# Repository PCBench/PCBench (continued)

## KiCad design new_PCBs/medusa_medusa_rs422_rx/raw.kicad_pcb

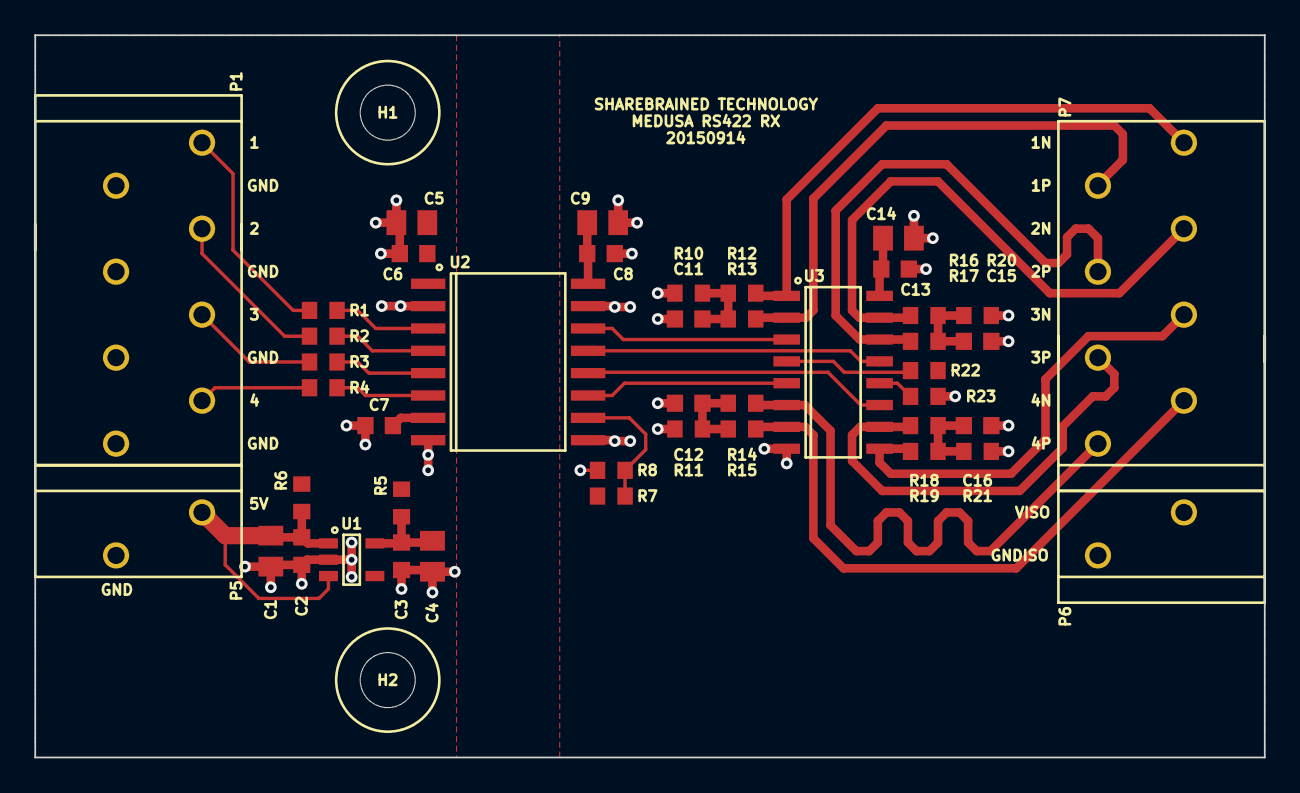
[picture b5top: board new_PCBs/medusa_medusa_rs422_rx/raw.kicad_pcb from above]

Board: 2 copper layers, 71.5 x 42.0 mm, 46 parts (0 on the bottom side), 33 nets.

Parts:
C1, C4: DNI; IPC_CAPC2012X140N
C2, C3: DNI; IPC_CAPC1608X95N
C5, C9, C14: 10U; IPC_CAPC2012X140N
C6, C7, C8, C13: 100N; IPC_CAPC1608X95N
C11, C12, C15, C16: 10N; IPC_CAPC1608X95N
H1, H2: HOLE; HOLE_3P2MM
P1, P7: TERM8; 1990067
P5, P6: TERM2; 1990009
R1, R2, R3, R4: 22R; IPC_RESC1608X55N
R5, R7, R10, R11, R20, R21: DNI; IPC_RESC1608X55N
R6, R8, R22, R23: 0R; IPC_RESC1608X55N
R12, R13, R14, R15, R16, R17, R18, R19: 50R; IPC_RESC1608X55N
U1: DNI; IPC_SOT95P280X110-5N
U2: ADuM6404; IPC_SOIC127P1030X265-16N
U3: AM26LV32E; IPC_SOIC127P600X175-16N

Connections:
+3.3V: C3.1, C4.1, R5.2, U1.5
+5V: C1.1, C2.1, P5.2, R6.2, U1.1, U1.3
/GNDISO: C8.2, C9.2, C11.1, C12.1, C13.2, C14.2, C15.2, C16.2, P6.2, R8.2, R10.1, R11.1, R20.2, R21.2, R23.2, U2.9, U2.15, U3.8
/RX1: R1.1, U2.3
/RX1ISO: U2.14, U3.3
/RX1N: P7.1, R12.2, U3.1
/RX1P: P7.2, R13.2, U3.2
/RX1R: P1.8, R1.2
/RX2: R2.1, U2.4
/RX2ISO: U2.13, U3.13
/RX2N: P7.3, R16.1, U3.15
/RX2P: P7.4, R17.1, U3.14
/RX2R: P1.6, R2.2
/RX3: R3.1, U2.5
/RX3ISO: U2.12, U3.11
/RX3N: P7.5, R19.1, U3.9
/RX3P: P7.6, R18.1, U3.10
/RX3R: P1.4, R3.2
/RX4: R4.1, U2.6
/RX4ISO: U2.11, U3.5
/RX4N: P7.7, R15.2, U3.7
/RX4P: P7.8, R14.2, U3.6
/RX4R: P1.2, R4.2
/RXG: R22.2, U3.4
/RXG#: R23.1, U3.12
/VDD1: C5.1, C6.1, C7.1, R5.1, R6.1, U2.1, U2.7
/VISO: C8.1, C9.1, C13.1, C14.1, P6.1, R7.2, R22.1, U2.16, U3.16
/VSEL: R7.1, R8.1, U2.10
GND: C1.2, C2.2, C3.2, C4.2, C5.2, C6.2, C7.2, P1.1, P1.3, P1.5, P1.7, P5.1, U1.2, U2.2, U2.8
unnamed: C11.2, R10.2, R12.1, R13.1
unnamed: C12.2, R11.2, R14.1, R15.1
unnamed: C15.1, R16.2, R17.2, R20.1
unnamed: C16.1, R18.2, R19.2, R21.1

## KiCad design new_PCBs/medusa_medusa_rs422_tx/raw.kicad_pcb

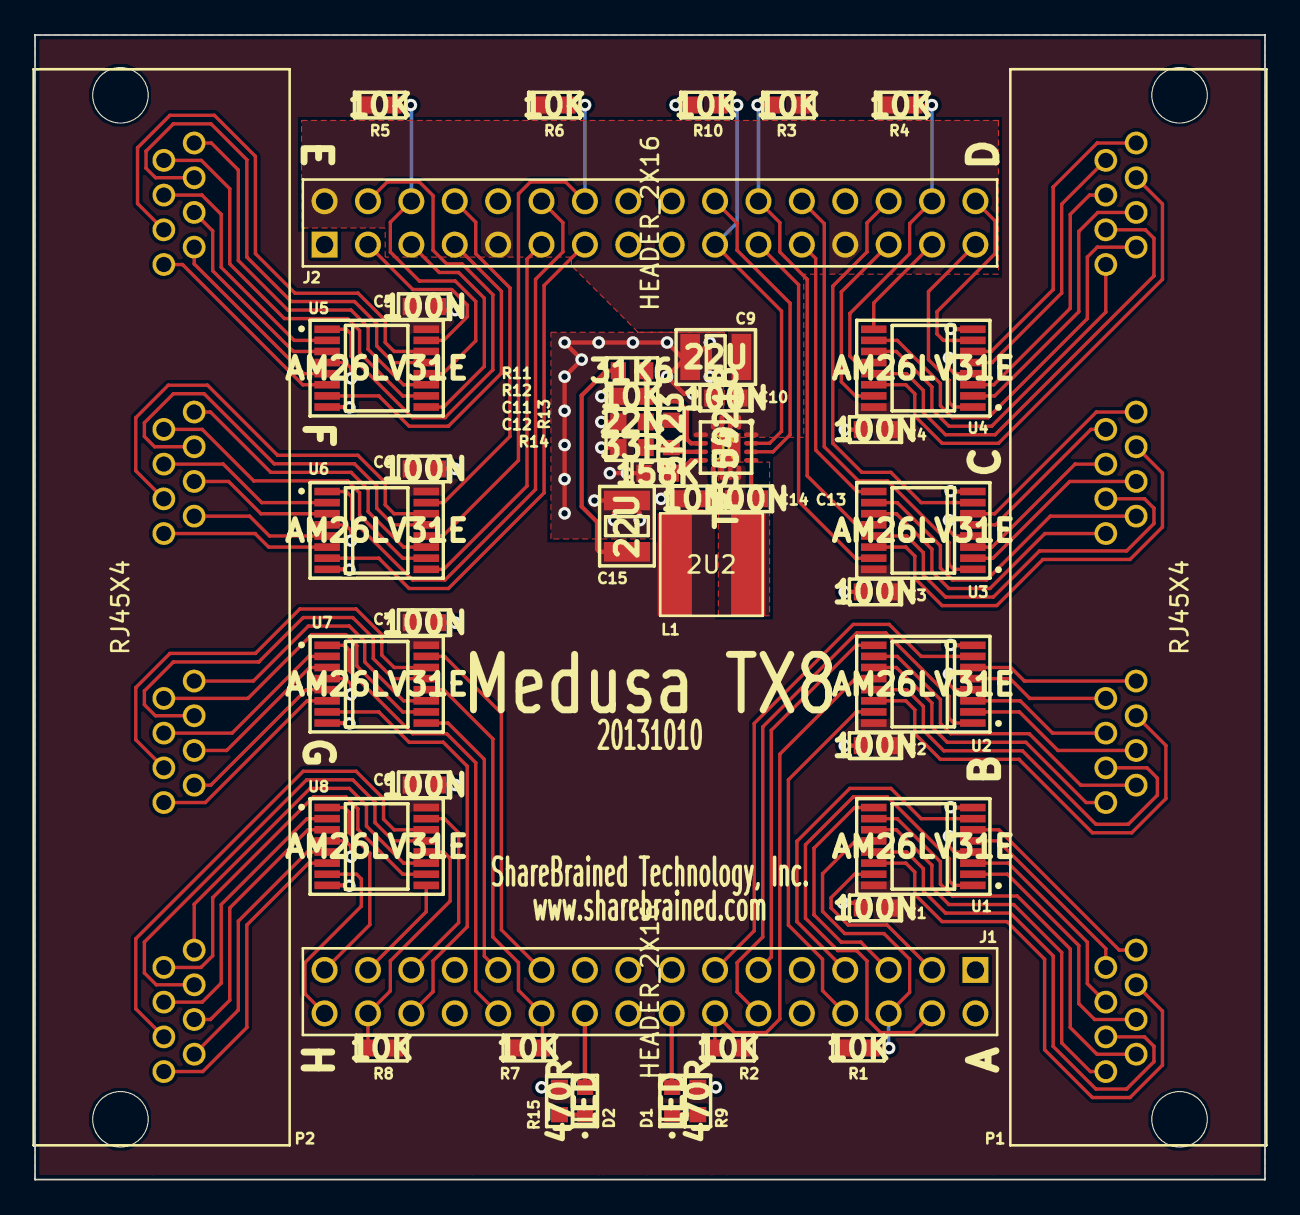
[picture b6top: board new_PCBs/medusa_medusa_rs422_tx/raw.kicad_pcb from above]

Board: 2 copper layers, 72.0 x 67.0 mm, 46 parts (0 on the bottom side), 120 nets.

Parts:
C1, C2, C3, C4, C5, C6, C7, C8, C10, C13: 100N; IPC_CAPC1608X95N
C9, C15: 22U; IPC_CAPC3225X270N
C11: 22N; IPC_CAPC1608X95N
C12: 33P; IPC_CAPC1608X95N
C14: 10N; IPC_CAPC1608X95N
D1, D2: LED; IPC_LEDC1608X60N
J1, J2: HEADER_2X16; HEADER_16X2_TH_254
L1: 2U2; BOURNS_SRN6045
P1, P2: RJ45X4; AMPHENOL_RJHSE508004
R1, R2, R3, R4, R5, R6, R7, R8, R10, R12: 10K; IPC_RESC1608X55N
R9, R15: 470R; IPC_RESC1608X55N
R11: 31K6; IPC_RESC1608X55N
R13: 5K23; IPC_RESC1608X55N
R14: 158K; IPC_RESC1608X55N
U1, U2, U3, U4, U5, U6, U7, U8: AM26LV31E; IPC_SOP65P640X120-16N
U9: TPS54218; TI_RTE_S-PWQFN-N16

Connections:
/AF0: J1.3, U1.15
/AF1: J1.4, U1.1
/AF2: J1.5, U1.9
/AF3: J1.7, U1.7
/AF4: J1.8, U2.15
/AF5: J1.11, U2.9
/AF6: J1.12, U2.1
/AF7: J1.13, U2.7
/AF9: D1.1, J1.16
/AF11: D2.1, J1.20
/AF12: J1.21, U7.15
/AF13: J1.23, U7.9
/AF14: J1.24, U7.1
/AF15: J1.27, U8.15
/AF16: J1.28, U7.7
/AF17: J1.29, U8.9
/AF18: J1.31, U8.1
/AF19: J1.32, U8.7
/AS0: J1.6, R1.1, U1.12
/AS1: J1.14, R2.1, U2.12
/AS2: J1.22, R7.1, U7.12
/AS3: J1.30, R8.1, U8.12
/BF0: J2.3, U5.15
/BF1: J2.4, U5.1
/BF2: J2.5, U5.9
/BF3: J2.7, U5.7
/BF4: J2.8, U6.15
/BF5: J2.11, U6.9
/BF6: J2.12, U6.1
/BF7: J2.13, U6.7
/BF10: J2.19, R10.2, U9.15
/BF11: J2.20, U9.14
/BF12: J2.21, U3.15
/BF13: J2.23, U3.9
/BF14: J2.24, U3.1
/BF15: J2.27, U4.15
/BF16: J2.28, U3.7
/BF17: J2.29, U4.9
/BF18: J2.31, U4.1
/BF19: J2.32, U4.7
/BS0: J2.6, R5.1, U5.12
/BS1: J2.14, R6.1, U6.12
/BS2: J2.22, R3.1, U3.12
/BS3: J2.30, R4.1, U4.12
/SWPH: C13.2, L1.2, U9.10, U9.11, U9.12
/TX0N: P1.A2, U1.5
/TX0P: P1.A1, U1.6
/TX1N: P1.A6, U1.13
/TX1P: P1.A3, U1.14
/TX2N: P1.A4, U1.3
/TX2P: P1.A5, U1.2
/TX3N: P1.A8, U1.11
/TX3P: P1.A7, U1.10
/TX4N: P1.B2, U2.5
/TX4P: P1.B1, U2.6
/TX5N: P1.B6, U2.13
/TX5P: P1.B3, U2.14
/TX6N: P1.B4, U2.3
/TX6P: P1.B5, U2.2
/TX7N: P1.B8, U2.11
/TX7P: P1.B7, U2.10
/TX8N: P1.C2, U3.5
/TX8P: P1.C1, U3.6
/TX9N: P1.C6, U3.13
/TX9P: P1.C3, U3.14
/TX10N: P1.C4, U3.3
/TX10P: P1.C5, U3.2
/TX11N: P1.C8, U3.11
/TX11P: P1.C7, U3.10
/TX12N: P1.D2, U4.5
/TX12P: P1.D1, U4.6
/TX13N: P1.D6, U4.13
/TX13P: P1.D3, U4.14
/TX14N: P1.D4, U4.3
/TX14P: P1.D5, U4.2
/TX15N: P1.D8, U4.11
/TX15P: P1.D7, U4.10
/TX16N: P2.A2, U5.5
/TX16P: P2.A1, U5.6
/TX17N: P2.A6, U5.13
/TX17P: P2.A3, U5.14
/TX18N: P2.A4, U5.3
/TX18P: P2.A5, U5.2
/TX19N: P2.A8, U5.11
/TX19P: P2.A7, U5.10
/TX20N: P2.B2, U6.5
/TX20P: P2.B1, U6.6
/TX21N: P2.B6, U6.13
/TX21P: P2.B3, U6.14
/TX22N: P2.B4, U6.3
/TX22P: P2.B5, U6.2
/TX23N: P2.B8, U6.11
/TX23P: P2.B7, U6.10
/TX24N: P2.C2, U7.5
/TX24P: P2.C1, U7.6
/TX25N: P2.C6, U7.13
/TX25P: P2.C3, U7.14
/TX26N: P2.C4, U7.3
/TX26P: P2.C5, U7.2
/TX27N: P2.C8, U7.11
/TX27P: P2.C7, U7.10
/TX28N: P2.D2, U8.5
/TX28P: P2.D1, U8.6
/TX29N: P2.D6, U8.13
/TX29P: P2.D3, U8.14
/TX30N: P2.D4, U8.3
/TX30P: P2.D5, U8.2
/TX31N: P2.D8, U8.11
/TX31P: P2.D7, U8.10
/VTX: C1.1, C2.1, C3.1, C4.1, C5.1, C6.1, C7.1, C8.1, C15.1, L1.1, R1.2, R2.2, R3.2, R4.2, R5.2, R6.2, R7.2, R8.2, R11.1, U1.16, U2.16, U3.16, U4.16, U5.16, U6.16, U7.16, U8.16
/V_RAW: C9.1, C10.1, J1.2, J1.9, J1.18, J1.25, J2.2, J2.9, J2.25, U9.1, U9.2, U9.16
GND: C1.2, C2.2, C3.2, C4.2, C5.2, C6.2, C7.2, C8.2, C9.2, C10.2, C11.2, C12.2, C14.2, C15.2, J1.1, J1.10, J1.17, J1.26, J2.1, J2.10, J2.17, J2.26, R9.1, R10.1, R12.1, R14.1, R15.1, U1.4, U1.8, U2.4, U2.8, U3.4, U3.8, U4.4, U4.8, U5.4, U5.8, U6.4, U6.8, U7.4, U7.8, U8.4, U8.8, U9.3, U9.4, U9.5, U9.17
Net-<C11-Pad1>: C11.1, R13.1
Net-<C12-Pad1>: C12.1, R13.2, U9.7
Net-<C13-Pad1>: C13.1, U9.13
Net-<C14-Pad1>: C14.1, U9.9
Net-<D1-Pad2>: D1.2, R9.2
Net-<D2-Pad2>: D2.2, R15.2
Net-<R11-Pad2>: R11.2, R12.2, U9.6
Net-<R14-Pad2>: R14.2, U9.8
